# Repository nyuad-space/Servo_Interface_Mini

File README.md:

# Servo Interface Mini

## Overview

The **Servo Interface Mini** is a compact, flight-proven board built around the ATmega328P. It controls two servos via PWM based on logic changes on pyro channels. The board is part of our custom rocket parachute deployment system called the **Hold-Down Release Mechanism (HDRM)**.

It translates changes on pyro outputs from a flight computer into servo movement that actuates deployment hardware.

## Features

* **Microcontroller**: ATmega328P running Arduino-compatible firmware
* **Dual PWM Outputs**: Drives two standard hobby servos
* **Pyro Channel Triggering**: Responds to logic transitions on pyro lines
* **Status Indicators**: Onboard LEDs for deployment and system debugging
* **Power Supply**: Integrated LDO regulator supplies up to **5A at 5V** to servos and logic
* **Programming**: FTDI header for serial programming
* **Form Factor**: Compact layout with mounting holes for rugged, enclosed deployment

## Applications

* Servo-based parachute deployment systems
* Signal translation between flight computers and actuators
* Compact automation setups in rocketry and UAV systems

## Programming

The board is Arduino-compatible and programmed over an FTDI serial connection.

1. **Board Selection**: Choose **Arduino Pro Mini (5V, 16 MHz)** in the Arduino IDE
2. **Upload Method**: Use an FTDI-to-USB adapter connected to the 6-pin header
3. **Bootloader**: Compatible with standard Arduino bootloaders for ATmega328P

## Future Improvements

* Switch to **ATmega32U4** for native USB support and remove the need for an FTDI adapter

## Notes

* Pyro channel inputs are pulled up to 5V
* Designed for flight computers that ground pyro outputs (open-drain or active-low)
* Make sure servo current does not exceed 5A limit of onboard regulator
* Double check servo travel range to avoid overdriving linkages

**Disclaimer**: Use the files, hardware, and software in this repository at your own risk. We accept no responsibility for damage, failure, or unexpected behavior, especially during live flight tests.

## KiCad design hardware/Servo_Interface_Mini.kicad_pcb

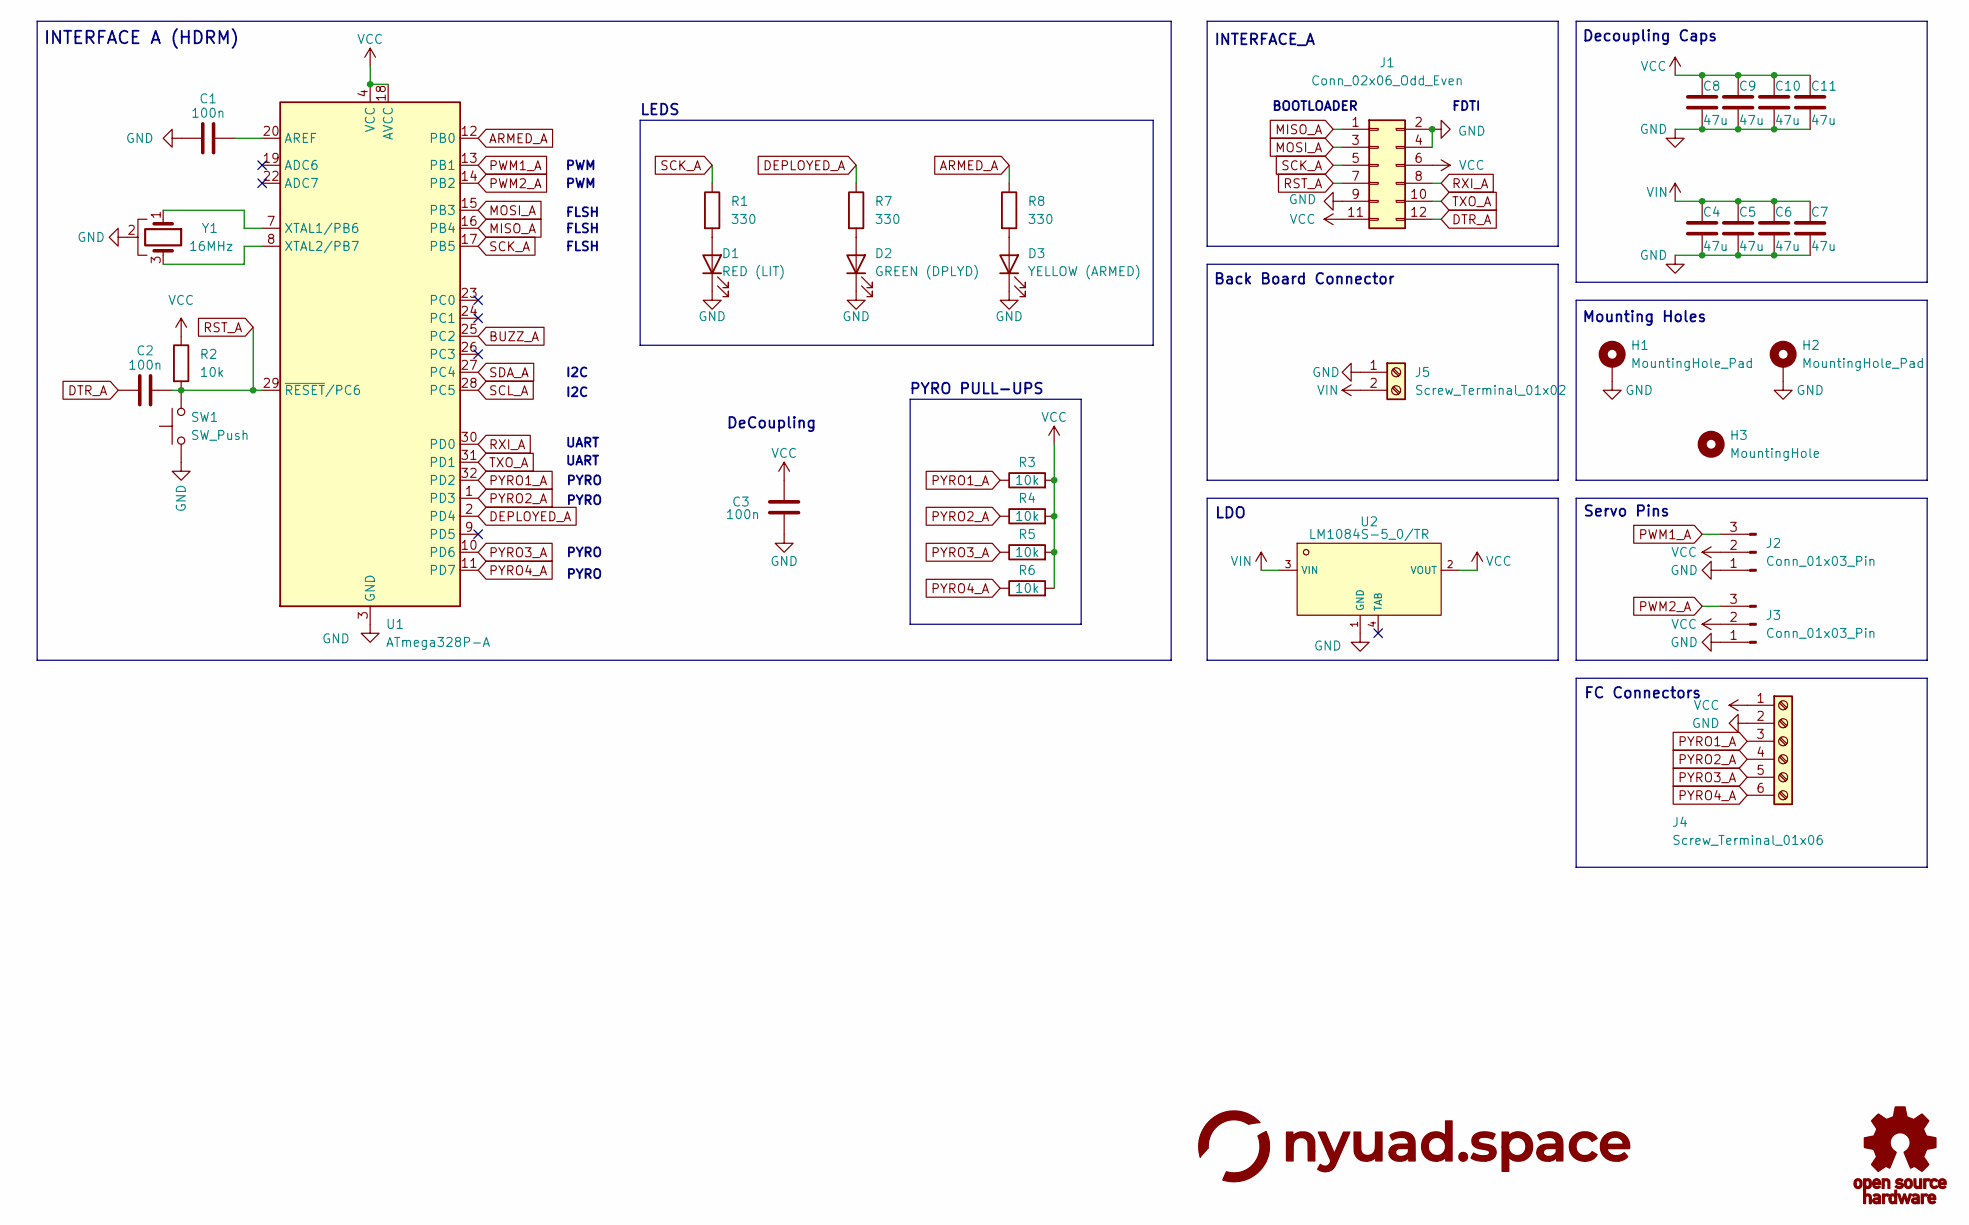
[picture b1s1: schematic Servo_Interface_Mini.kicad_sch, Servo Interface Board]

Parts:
C1, C2, C3: 100n; C_0402_1005Metric
C4, C5, C6, C7, C8, C9, C10, C11: 47u; C_0805_2012Metric
D1: RED (LIT); LED_0402_1005Metric
D2: GREEN (DPLYD); LED_0402_1005Metric
D3: YELLOW (ARMED); LED_0402_1005Metric
H1, H2: MountingHole_Pad; MountingHole_2.7mm_M2.5_Pad_Via
H3: MountingHole; MountingHole_2.7mm
J1: Conn_02x06_Odd_Even; HDR-TH_12P-P2.54-V-F-R2-C6-S2.54
J2, J3: Conn_01x03_Pin; PinHeader_1x03_P2.54mm_Horizontal
J4: Screw_Terminal_01x06; CONN-TH_DB125-2.54-6P-GN
J5: Screw_Terminal_01x02; CONN-TH_DB125-2.54-2P-GN
R1, R7, R8: 330; R_0402_1005Metric
R2, R3, R4, R5, R6: 10k; R_0402_1005Metric
SW1: SW_Push; SW_SPST_B3U-1000P
U1: ATmega328P-A; TQFP-32_7x7mm_P0.8mm
U2: LM1084S-5_0/TR; TO-263-3_L8.6-W10.2-P2.54-LS14.4-TL; LCSC C259973
Y1: 16MHz; OSC-SMD_3P-L3.2-W1.3-P0.95-L

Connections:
ARMED_A: R8.1, U1.12 (PB0)
BUZZ_A: U1.25 (PC2)
DEPLOYED_A: R7.1, U1.2 (PD4)
DTR_A: C2.1, J1.12
GND: C1.1, C3.1, C4.2, C5.2, C6.2, C7.2, C8.2, C9.2, C10.2, C11.2, D1.1 (K), D2.1 (K), D3.1 (K), H1.1, H2.1, J1.2, J1.4, J1.9, J2.1, J3.1, J4.2, J5.1, SW1.1, U1.3 (GND), U1.5 (GND), U1.21 (GND), U2.1 (GND), Y1.2
MISO_A: J1.1, U1.16 (PB4)
MOSI_A: J1.3, U1.15 (PB3)
unnamed: D1.2 (A), R1.2
unnamed: D2.2 (A), R7.2
unnamed: D3.2 (A), R8.2
unnamed: C1.2, U1.20 (AREF)
unnamed: U1.7 (XTAL1/PB6), Y1.1
unnamed: U1.8 (XTAL2/PB7), Y1.3
PWM1_A: J2.3, U1.13 (PB1)
PWM2_A: J3.3, U1.14 (PB2)
PYRO1_A: J4.3, R3.1, U1.32 (PD2)
PYRO2_A: J4.4, R4.1, U1.1 (PD3)
PYRO3_A: J4.5, R5.1, U1.10 (PD6)
PYRO4_A: J4.6, R6.1, U1.11 (PD7)
RST_A: C2.2, J1.7, R2.2, SW1.2, U1.29 (~RESET/PC6)
RXI_A: J1.8, U1.30 (PD0)
SCK_A: J1.5, R1.1, U1.17 (PB5)
SCL_A: U1.28 (PC5)
SDA_A: U1.27 (PC4)
TXO_A: J1.10, U1.31 (PD1)
VCC: C3.2, C8.1, C9.1, C10.1, C11.1, J1.6, J1.11, J2.2, J3.2, J4.1, R2.1, R3.2, R4.2, R5.2, R6.2, U1.4 (VCC), U1.6 (VCC), U1.18 (AVCC), U2.2 (VOUT)
VIN: C4.1, C5.1, C6.1, C7.1, J5.2, U2.3 (VIN)

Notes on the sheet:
FC Connectors
Servo Pins
Decoupling Caps
DeCoupling
FLSH
LEDS
UART
Back Board Connector
PYRO PULL-UPS
I2C
PYRO
INTERFACE A (HDRM)
PWM
LDO
Mounting Holes
FDTI
BOOTLOADER
INTERFACE_A

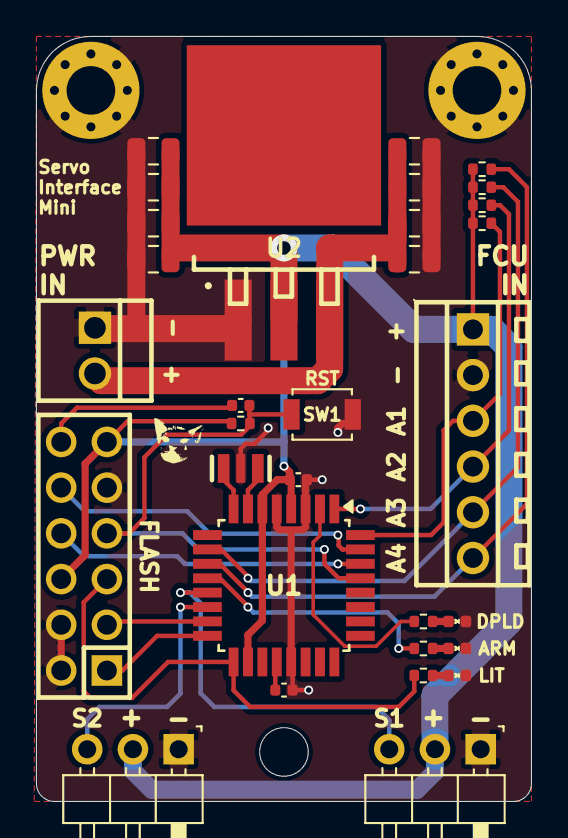
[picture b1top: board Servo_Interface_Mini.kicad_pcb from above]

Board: 2 copper layers, 27.5 x 42.5 mm, 34 parts (0 on the bottom side), 24 nets.
